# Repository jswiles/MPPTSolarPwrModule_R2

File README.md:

# MPPTSolarPwrModule_R2

MPPT Solar Power Module Revision 2

- 3.7V LiPo cell
- INA3221 Current/Voltage Monitor
    - Solar Panel Input
    - Battery Cell Output
    - Load Output 
- 6V/12V Solar Panel Selection
- Load Sharing of Solar Panel and Battery
- Regulated 6V output

Revision 2 prototype and test using Revision 1 board.

Revision 2 3D Model

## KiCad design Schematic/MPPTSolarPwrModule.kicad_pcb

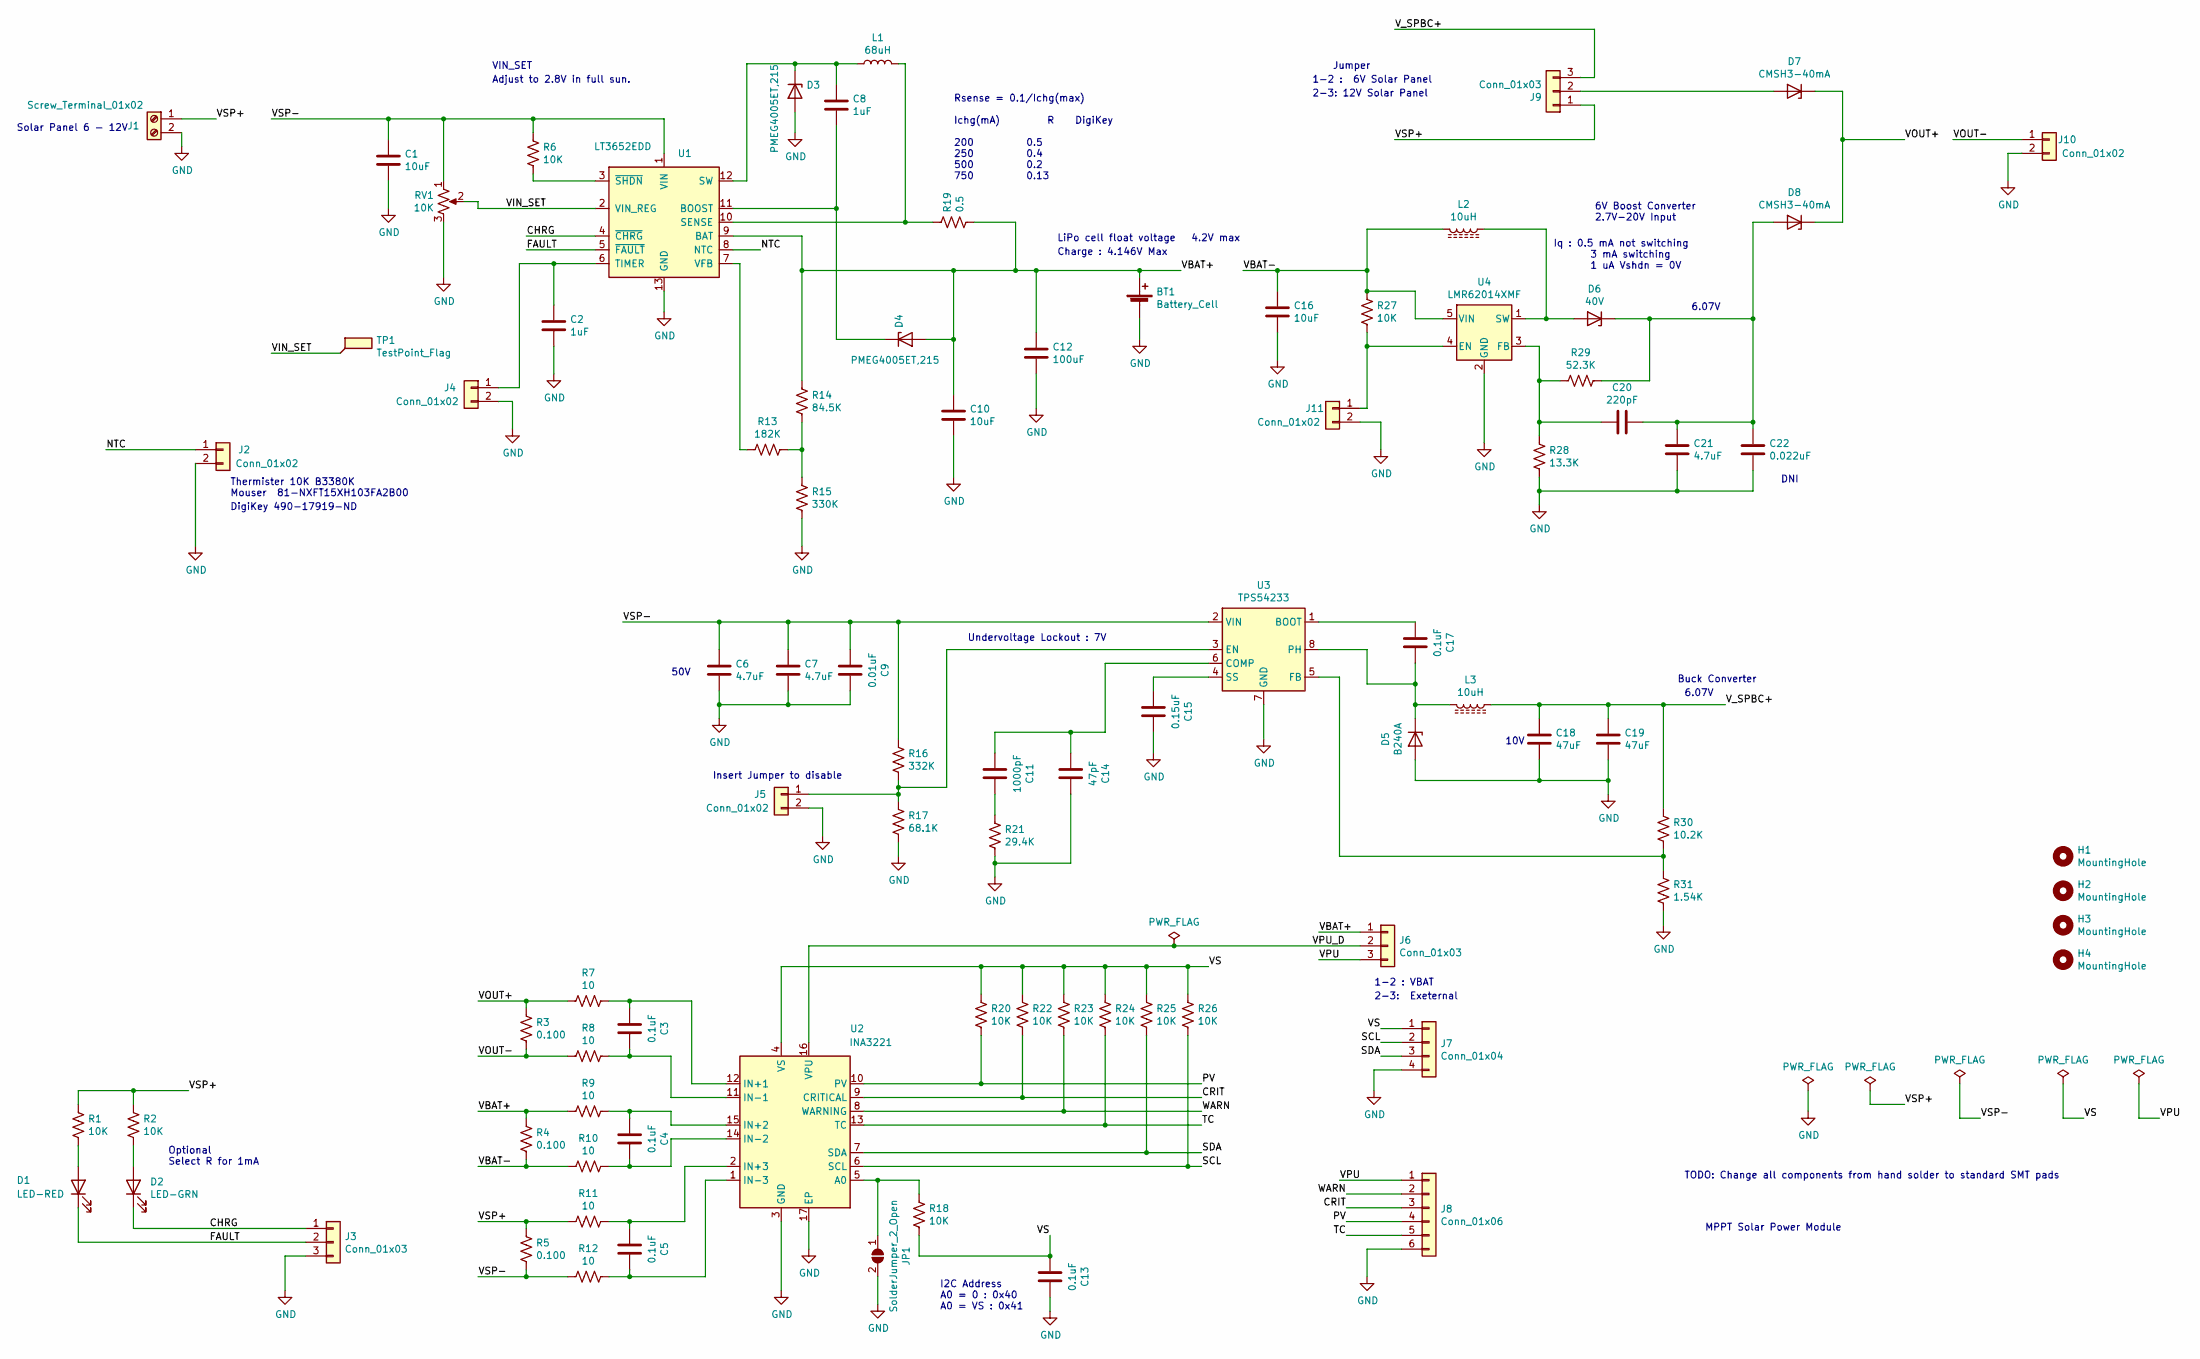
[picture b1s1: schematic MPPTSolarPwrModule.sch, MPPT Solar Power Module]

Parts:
BT1: Battery_Cell; BatteryHolder_Keystone_1042_1x18650; Mouser 534-1042
C1, C10, C16: 10uF; C_1210_3225Metric; DigiKey 587-1965-1-ND
C2, C8: 1uF; C_0805_2012Metric; DigiKey 445-6961-1-ND
C3, C4, C5, C13, C17: 0.1uF; C_0603_1608Metric
C6, C7: 4.7uF; C_1210_3225Metric; Mouser 603-CC1210KFX7R9B475
C9: 0.01uF; C_0603_1608Metric
C11: 1000pF; C_0603_1608Metric
C12: 100uF; C_1210_3225Metric; DigiKey 587-1965-1-ND
C14: 47pF; C_0603_1608Metric
C15: 0.15uF; C_0603_1608Metric
C18, C19: 47uF; C_1206_3216Metric
C20: 220pF; C_0603_1608Metric; Mouser 346-CM21X5R475K25AT
C21: 4.7uF; C_1210_3225Metric; DigiKey 490-1864-1-ND
C22: 0.022uF; C_0603_1608Metric; DigiKey 490-3884-1-ND
D1: LED-RED; LED_0805_2012Metric; DigiKey 754-1128-1-ND
D2: LED-GRN; LED_0805_2012Metric; DigiKey 754-1795-1-ND
D3, D4: PMEG4005ET,215; D_SOT-23_ANK; DigiKey 1727-3878-1-ND
D5: B240A; D_SMA
D6: 40V; D_SOD-123; DigiKey RB168MM-40CT-ND
D7, D8: CMSH3-40mA; D_SMA; DigiKey 1514-CMSH3-40MATR13PBFREECT-ND
H1, H2, H3, H4: MountingHole; MountingHole_2.5mm
J1: Screw_Terminal_01x02; TerminalBlock_Phoenix_MPT-0,5-2-2.54_1x02_P2.54mm_Horizontal; Mouser 651-1725656
J2, J4, J5, J11: Conn_01x02; PinHeader_1x02_P2.54mm_Vertical
J3: Conn_01x03; JST_EH_B3B-EH-A_1x03_P2.50mm_Vertical
J6, J9: Conn_01x03; PinHeader_1x03_P2.54mm_Vertical
J7: Conn_01x04; JST_EH_B4B-EH-A_1x04_P2.50mm_Vertical
J8: Conn_01x06; JST_EH_B6B-EH-A_1x06_P2.50mm_Vertical
J10: Conn_01x02; JST_EH_B2B-EH-A_1x02_P2.50mm_Vertical
JP1: SolderJumper_2_Open; SolderJumper-2_P1.3mm_Open_RoundedPad1.0x1.5mm
L1: 68uH; L_Bourns_SRR1260; DigiKey SRR1260-680MCT-ND
L2, L3: 10uH; L_Bourns_SRN6045TA; DigiKey SRN6045-100MCT-ND
R1, R2, R6: 10K; R_0805_2012Metric; DigiKey RMCF0805JT10K0CT-ND
R3, R4, R5: 0.100; R_1206_3216Metric
R7, R8, R9, R10, R11, R12: 10; R_0603_1608Metric
R13: 182K; R_0805_2012Metric
R14: 84.5K; R_0805_2012Metric
R15: 330K; R_0805_2012Metric
R16: 332K; R_0805_2012Metric; DigiKey RMCF0805JT10K0CT-ND
R17: 68.1K; R_0805_2012Metric; DigiKey RMCF0805JT10K0CT-ND
R18, R20, R22, R23, R24, R25, R26: 10K; R_0603_1608Metric; DigiKey RMCF0805JT10K0CT-ND
R19: 0.5; R_1206_3216Metric_Pad1.30x1.75mm_HandSolder; DigiKey 13-RL1206FR-7W0R5LCT-ND
R21: 29.4K; R_0805_2012Metric; DigiKey RMCF0805JT10K0CT-ND
R27: 10K; R_0603_1608Metric
R28: 13.3K; R_0603_1608Metric; DigiKey CRCW060313K3FKEA
R29: 52.3K; R_0603_1608Metric
R30: 10.2K; R_0805_2012Metric; DigiKey RMCF0805JT10K0CT-ND
R31: 1.54K; R_0805_2012Metric; DigiKey RMCF0805JT10K0CT-ND
RV1: 10K; Potentiometer_Bourns_3386F_Vertical; DigiKey 3386F-103LF-ND
TP1: TestPoint_Flag; TestPoint_THTPad_1.5x1.5mm_Drill0.7mm
U1: LT3652EDD; MSOP-12-1EP_3x4mm_P0.65mm_EP1.65x2.85mm; DigiKey LT3652HVEDD#PBF-ND
U2: INA3221; Texas_RGV_S-PVQFN-N16_EP2.1x2.1mm
U3: TPS54233; SOIC-8_3.9x4.9mm_P1.27mm
U4: LMR62014XMF; SOT-23-5; DigiKey LMR62014XMF/NOPBCT-ND

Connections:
/CHRG: D2.1 (K), J3.1, U1.4 (~CHRG)
/CRIT: J8.3, R22.2, U2.9 (CRITICAL)
/FAULT: D1.1 (K), J3.2, U1.5 (~FAULT)
/NTC: J2.1, U1.8 (NTC)
/PV: J8.4, R20.2, U2.10 (PV)
/SCL: J7.2, R26.2, U2.6 (SCL)
/SDA: J7.3, R25.2, U2.7 (SDA)
/TC: J8.5, R24.2, U2.13 (TC)
/VBAT+: BT1.1 (+), C10.1, C12.1, D4.2 (A), J6.1, R4.1, R9.2, R14.1, R19.2, U1.9 (BAT)
/VBAT-: C16.1, L2.2, R4.2, R10.2, R27.1, U4.5 (VIN)
/VIN_SET: RV1.2, TP1.1, U1.2 (VIN_REG)
/VOUT+: D7.1 (K), D8.1 (K), R3.1, R7.2
/VOUT-: J10.1, R3.2, R8.2
/VPU: J6.3, J8.1
/VPU_D: J6.2, U2.16 (VPU)
/VS: C13.2, J7.1, R18.2, R20.1, R22.1, R23.1, R24.1, R25.1, R26.1, U2.4 (VS)
/VSP+: J1.1, J9.1, R1.1, R2.1, R5.1, R11.2
/VSP-: C1.1, C6.1, C7.1, C9.2, R5.2, R6.1, R12.2, R16.1, RV1.1, U1.1 (VIN), U3.2 (VIN)
/V_SPBC+: C18.1, C19.1, J9.3, L3.1, R30.1
/WARN: J8.2, R23.2, U2.8 (WARNING)
GND: BT1.2 (-), C1.2, C2.2, C6.2, C7.2, C9.1, C10.2, C12.2, C13.1, C14.1, C15.1, C16.2, C18.2, C19.2, C21.2, C22.2, D3.2 (A), D5.2 (A), J1.2, J2.2, J3.3, J4.2, J5.2, J7.4, J8.6, J10.2, J11.2, JP1.2 (B), R15.2, R17.2, R21.2, R28.2, R31.2, RV1.3, U1.13 (GND), U2.3 (GND), U2.17 (EP), U3.7 (GND), U4.2 (GND)
unnamed: C2.1, J4.1, U1.6 (TIMER)
unnamed: C3.1, R8.1, U2.11 (IN-1)
unnamed: C3.2, R7.1, U2.12 (IN+1)
unnamed: C4.1, R10.1, U2.14 (IN-2)
unnamed: C4.2, R9.1, U2.15 (IN+2)
unnamed: C5.1, R12.1, U2.1 (IN-3)
unnamed: C5.2, R11.1, U2.2 (IN+3)
unnamed: C8.1, D3.1 (K), L1.1, U1.12 (SW)
unnamed: C8.2, D4.1 (K), U1.11 (BOOST)
unnamed: C11.1, R21.1
unnamed: C11.2, C14.2, U3.6 (COMP)
unnamed: C15.2, U3.4 (SS)
unnamed: C17.1, D5.1 (K), L3.2, U3.8 (PH)
unnamed: C17.2, U3.1 (BOOT)
unnamed: C20.1, C21.1, C22.1, D6.1 (K), D8.2 (A), R29.1
unnamed: C20.2, R28.1, R29.2, U4.3 (FB)
unnamed: D1.2 (A), R1.2
unnamed: D2.2 (A), R2.2
unnamed: D6.2 (A), L2.1, U4.1 (SW)
unnamed: D7.2 (A), J9.2
unnamed: J5.1, R16.2, R17.1, U3.3 (EN)
unnamed: J11.1, R27.2, U4.4 (EN)
unnamed: JP1.1 (A), R18.1, U2.5 (A0)
unnamed: L1.2, R19.1, U1.10 (SENSE)
unnamed: R6.2, U1.3 (~SHDN)
unnamed: R13.1, R14.2, R15.1
unnamed: R13.2, U1.7 (VFB)
unnamed: R30.2, R31.1, U3.5 (FB)

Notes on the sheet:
6V Boost Converter 2.7V-20V Input
Thermister 10K B3380K Mouser 81-NXFT15XH103FA2B00
DigiKey 490-17919-ND
Solar Panel 6 - 12V
Optional Select R for 1mA
Rsense = 0.1/Ichg(max) Ichg(mA) R DigiKey 200 0.5 250 0.4 500 0.2 750 0.13
LiPo cell float voltage 4.2V max
DNI
Buck Converter
VIN_SET
Adjust to 2.8V in full sun.
Charge : 4.146V Max
6.07V
1-2 : 6V Solar Panel
2-3: 12V Solar Panel
Jumper
10V
50V
Iq : 0.5 mA not switching 3 mA switching 1 uA Vshdn = 0V
MPPT Solar Power Module
I2C Address A0 = 0 : 0x40 A0 = VS : 0x41
Insert Jumper to disable
Undervoltage Lockout : 7V
1-2 : VBAT
2-3: Exeternal
TODO: Change all components from hand solder to standard SMT pads

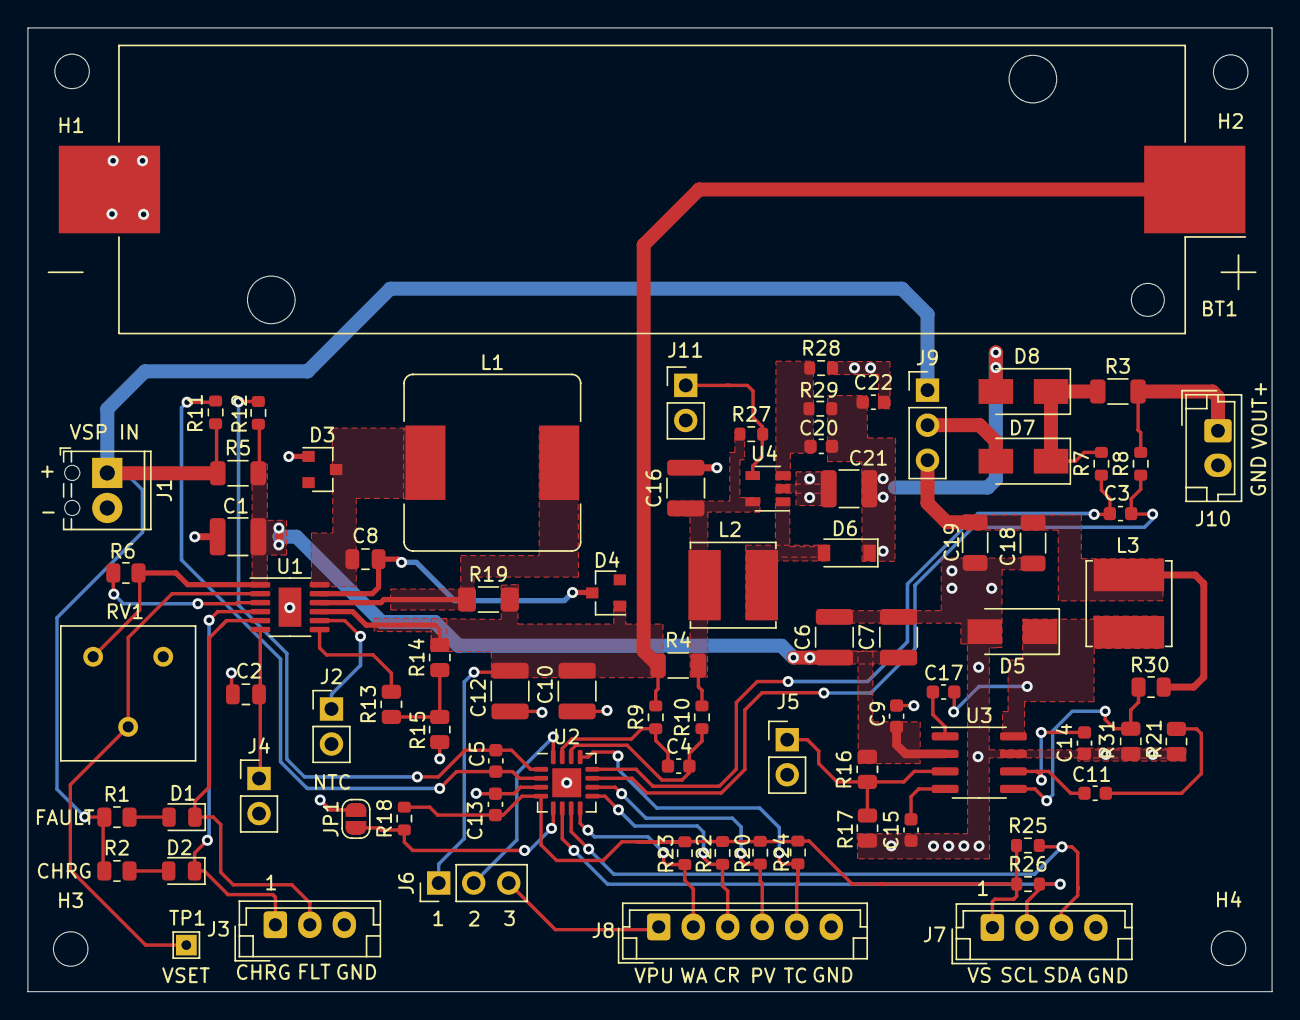
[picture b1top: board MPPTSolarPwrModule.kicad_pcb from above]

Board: 4 copper layers, 90.2 x 69.8 mm, 87 parts (0 on the bottom side), 49 nets.

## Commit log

2022-07-31 Added photos
2022-07-31 Add path to photosw
2022-07-31 Updated R2 3D JPG
2022-07-31 Added BOM, PCB and Schematics
2022-08-01 Added KiCad 3D models, Documents, and updated schematic
